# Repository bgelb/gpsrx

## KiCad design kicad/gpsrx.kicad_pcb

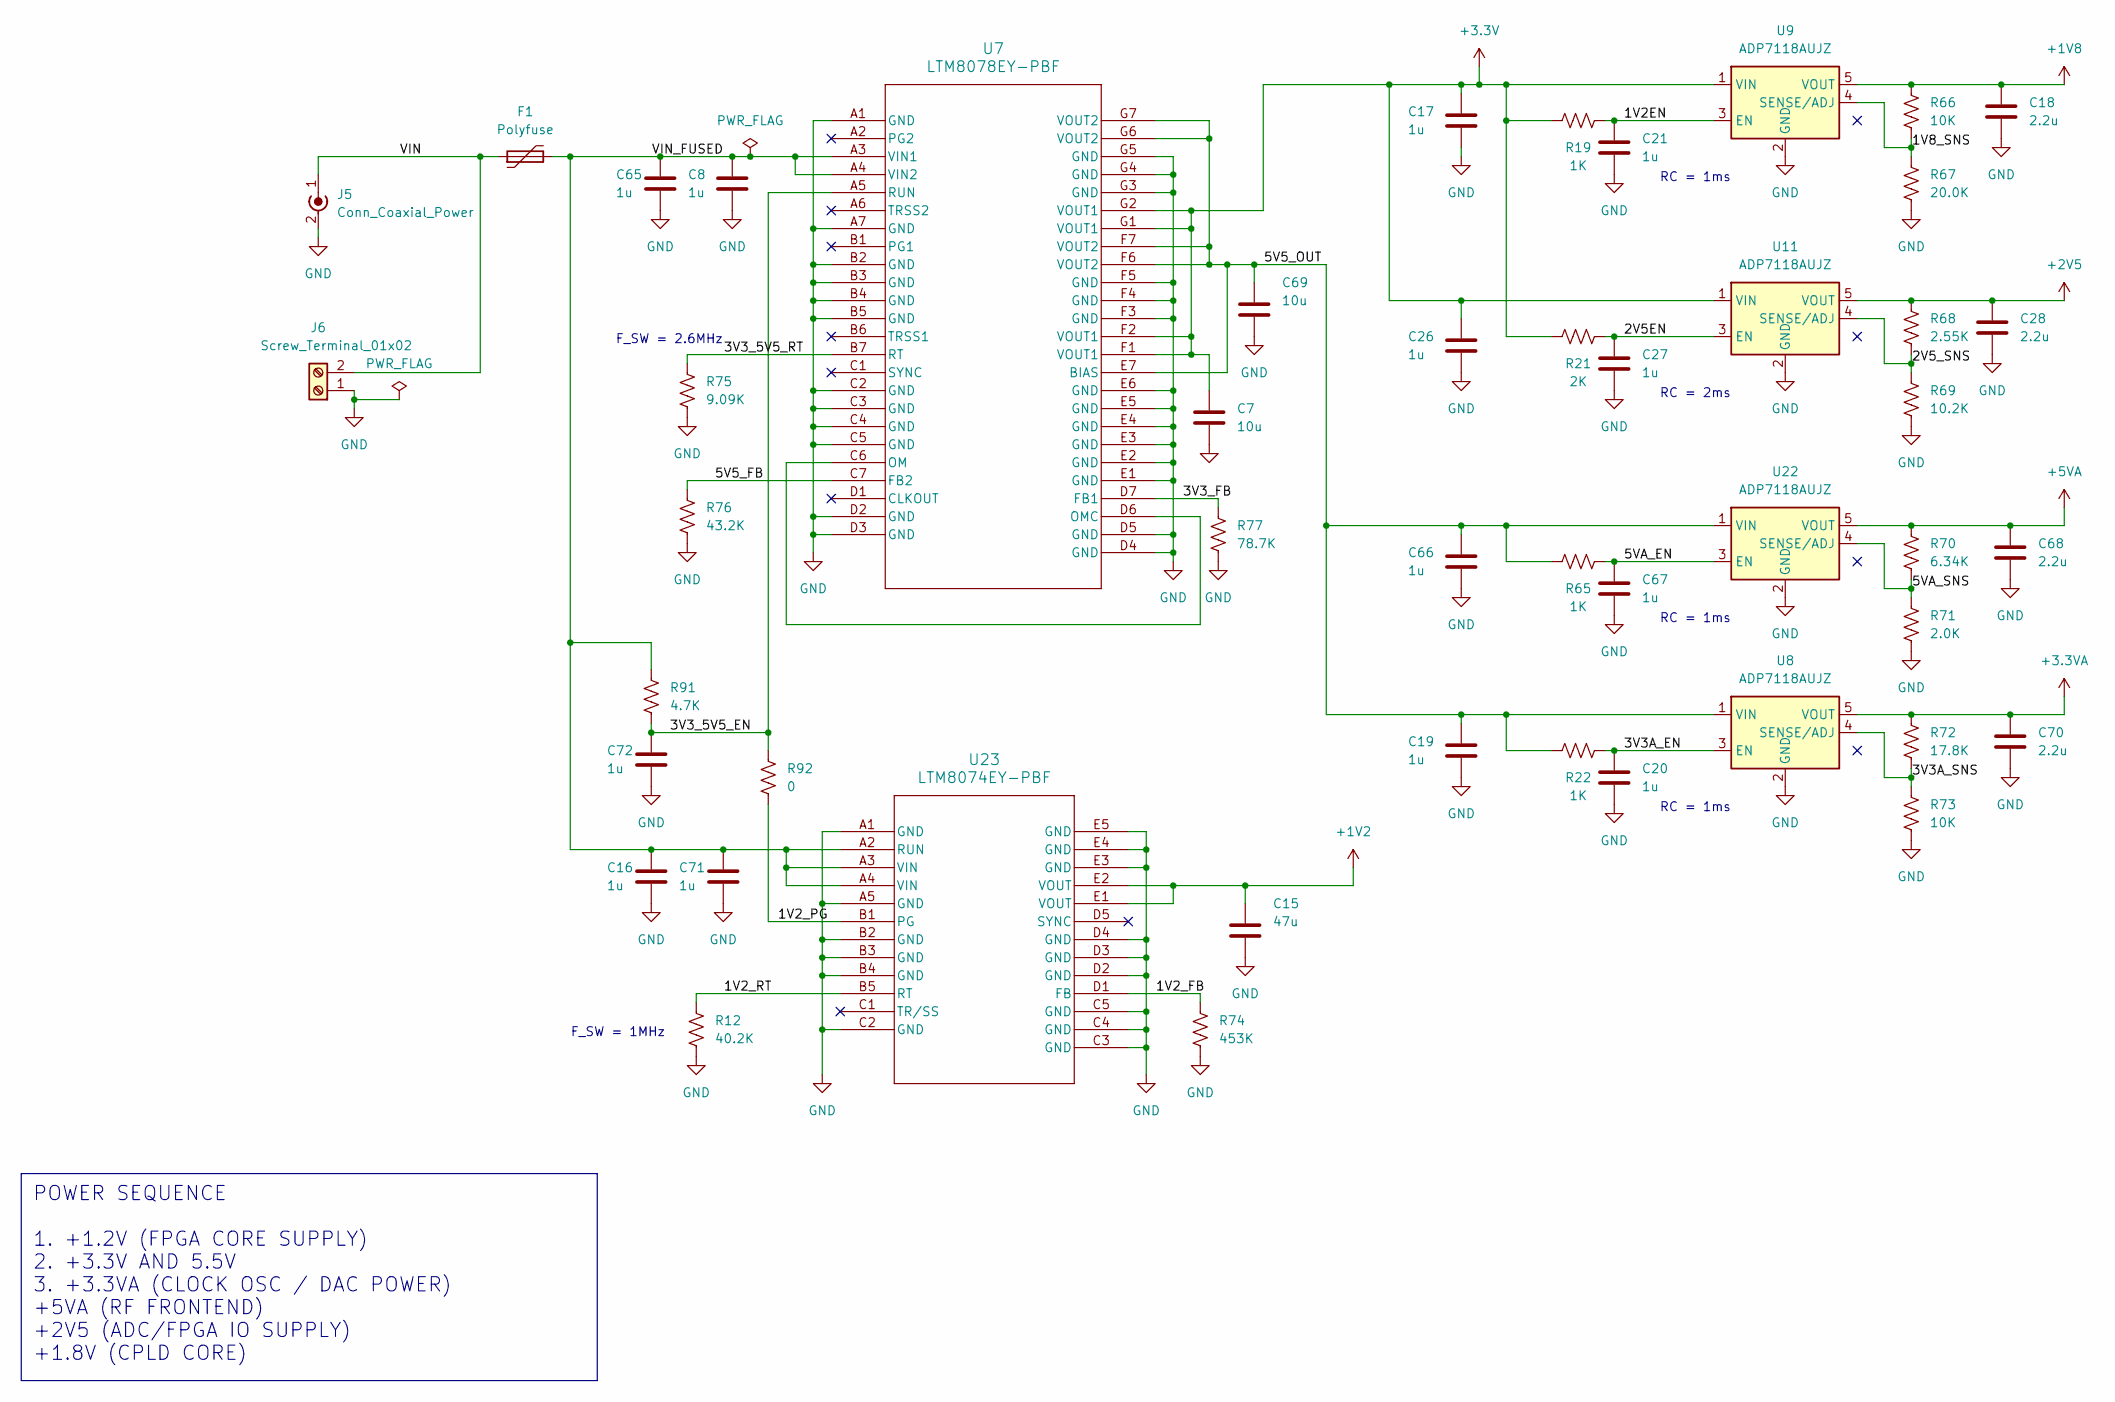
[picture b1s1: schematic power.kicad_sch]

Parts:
C7, C69: 10u; C_0805_2012Metric_Pad1.18x1.45mm_HandSolder
C8, C16, C17, C19, C20, C21, C26, C27, C65, C66, C67, C71, C72: 1u; C_0603_1608Metric_Pad1.08x0.95mm_HandSolder
C15: 47u; C_0805_2012Metric_Pad1.18x1.45mm_HandSolder
C18, C28, C68, C70: 2.2u; C_0603_1608Metric_Pad1.08x0.95mm_HandSolder
F1: Polyfuse; Fuse_2920_7451Metric_Pad2.10x5.45mm_HandSolder
J5: Conn_Coaxial_Power; BarrelJack_CUI_PJ-063AH_Horizontal
J6: Screw_Terminal_01x02; TerminalBlock_Phoenix_MKDS-1,5-2_1x02_P5.00mm_Horizontal
R12: 40.2K; R_0603_1608Metric_Pad0.98x0.95mm_HandSolder
R19, R22, R65: 1K; R_0603_1608Metric_Pad0.98x0.95mm_HandSolder
R21: 2K; R_0603_1608Metric_Pad0.98x0.95mm_HandSolder
R66, R73: 10K; R_0603_1608Metric_Pad0.98x0.95mm_HandSolder
R67: 20.0K; R_0603_1608Metric_Pad0.98x0.95mm_HandSolder
R68: 2.55K; R_0603_1608Metric_Pad0.98x0.95mm_HandSolder
R69: 10.2K; R_0603_1608Metric_Pad0.98x0.95mm_HandSolder
R70: 6.34K; R_0603_1608Metric_Pad0.98x0.95mm_HandSolder
R71: 2.0K; R_0603_1608Metric_Pad0.98x0.95mm_HandSolder
R72: 17.8K; R_0603_1608Metric_Pad0.98x0.95mm_HandSolder
R74: 453K; R_0603_1608Metric_Pad0.98x0.95mm_HandSolder
R75: 9.09K; R_0603_1608Metric_Pad0.98x0.95mm_HandSolder
R76: 43.2K; R_0603_1608Metric_Pad0.98x0.95mm_HandSolder
R77: 78.7K; R_0603_1608Metric_Pad0.98x0.95mm_HandSolder
R91: 4.7K; R_0603_1608Metric_Pad0.98x0.95mm_HandSolder
R92: 0; R_0603_1608Metric_Pad0.98x0.95mm_HandSolder
U7: LTM8078EY-PBF; LTM8078IY-PBF_ADI
U8, U9, U11, U22: ADP7118AUJZ; UJ_5_ADI
U23: LTM8074EY-PBF; 05-08-1566_ADI

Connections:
+1V2: C15.1, U23.E1 (VOUT), U23.E2 (VOUT); also elsewhere on the board
+1V8: C18.1, R66.1, U9.5 (VOUT); also elsewhere on the board
+2V5: C28.1, R68.1, U11.5 (VOUT); also elsewhere on the board
+3.3VA: C70.1, R72.1, U8.5 (VOUT); also elsewhere on the board
+5VA: C68.1, R70.1, U22.5 (VOUT); also elsewhere on the board
/Power/1V2EN: C21.1, R19.2, U9.3 (EN)
/Power/1V2_FB: R74.1, U23.D1 (FB)
/Power/1V2_PG: R92.2, U23.B1 (PG)
/Power/1V2_RT: R12.1, U23.B5 (RT)
/Power/1V8_SNS: R66.2, R67.1, U9.4 (SENSE/ADJ)
/Power/2V5EN: C27.1, R21.2, U11.3 (EN)
/Power/2V5_SNS: R68.2, R69.1, U11.4 (SENSE/ADJ)
/Power/3V3A_EN: C20.1, R22.2, U8.3 (EN)
/Power/3V3A_SNS: R72.2, R73.1, U8.4 (SENSE/ADJ)
/Power/3V3_5V5_EN: C72.1, R91.2, R92.1, U7.A5 (RUN)
/Power/3V3_5V5_RT: R75.1, U7.B7 (RT)
/Power/3V3_FB: R77.1, U7.D7 (FB1)
/Power/5V5_FB: R76.1, U7.C7 (FB2)
/Power/5V5_OUT: C19.1, C66.1, C69.1, R22.1, R65.1, U7.E7 (BIAS), U7.F6 (VOUT2), U7.F7 (VOUT2), U7.G6 (VOUT2), U7.G7 (VOUT2), U8.1 (VIN), U22.1 (VIN)
/Power/5VA_EN: C67.1, R65.2, U22.3 (EN)
/Power/5VA_SNS: R70.2, R71.1, U22.4 (SENSE/ADJ)
/Power/VIN: F1.1, J5.1 (In), J6.2
/Power/VIN_FUSED: C8.1, C16.1, C65.1, C71.1, F1.2, R91.1, U7.A3 (VIN1), U7.A4 (VIN2), U23.A2 (RUN), U23.A3 (VIN), U23.A4 (VIN)
GND: C7.2, C8.2, C15.2, C16.2, C17.2, C18.2, C19.2, C20.2, C21.2, C26.2, C27.2, C28.2, C65.2, C66.2, C67.2, C68.2, C69.2, C70.2, C71.2, C72.2, J5.2 (Ext), J6.1, R12.2, R67.2, R69.2, R71.2, R73.2, R74.2, R75.2, R76.2, R77.2, U7.A1 (GND), U7.A7 (GND), U7.B2 (GND), U7.B3 (GND), U7.B4 (GND), U7.B5 (GND), U7.C2 (GND), U7.C3 (GND), U7.C4 (GND), U7.C5 (GND), U7.D2 (GND), U7.D3 (GND), U7.D4 (GND), U7.D5 (GND), U7.E1 (GND), U7.E2 (GND), U7.E3 (GND), U7.E4 (GND), U7.E5 (GND), U7.E6 (GND), U7.F3 (GND), U7.F4 (GND), U7.F5 (GND), U7.G3 (GND), U7.G4 (GND), U7.G5 (GND), U8.2 (GND), U9.2 (GND), U11.2 (GND), U22.2 (GND), U23.A1 (GND), U23.A5 (GND), U23.B2 (GND), U23.B3 (GND), U23.B4 (GND), U23.C2 (GND), U23.C3 (GND), U23.C4 (GND), U23.C5 (GND), U23.D2 (GND), U23.D3 (GND), U23.D4 (GND), U23.E3 (GND), U23.E4 (GND), U23.E5 (GND); also elsewhere on the board
unnamed: U7.C6 (OM), U7.D6 (OMC)

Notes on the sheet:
POWER SEQUENCE 1. +1.2V (FPGA CORE SUPPLY) 2. +3.3V AND 5.5V 3. +3.3VA (CLOCK OSC / DAC POWER) +5VA (RF FRONTEND) +2V5 (ADC/FPGA IO SUPPLY) +1.8V (CPLD CORE)
F_SW = 2.6MHz
RC = 2ms
F_SW = 1MHz
RC = 1ms

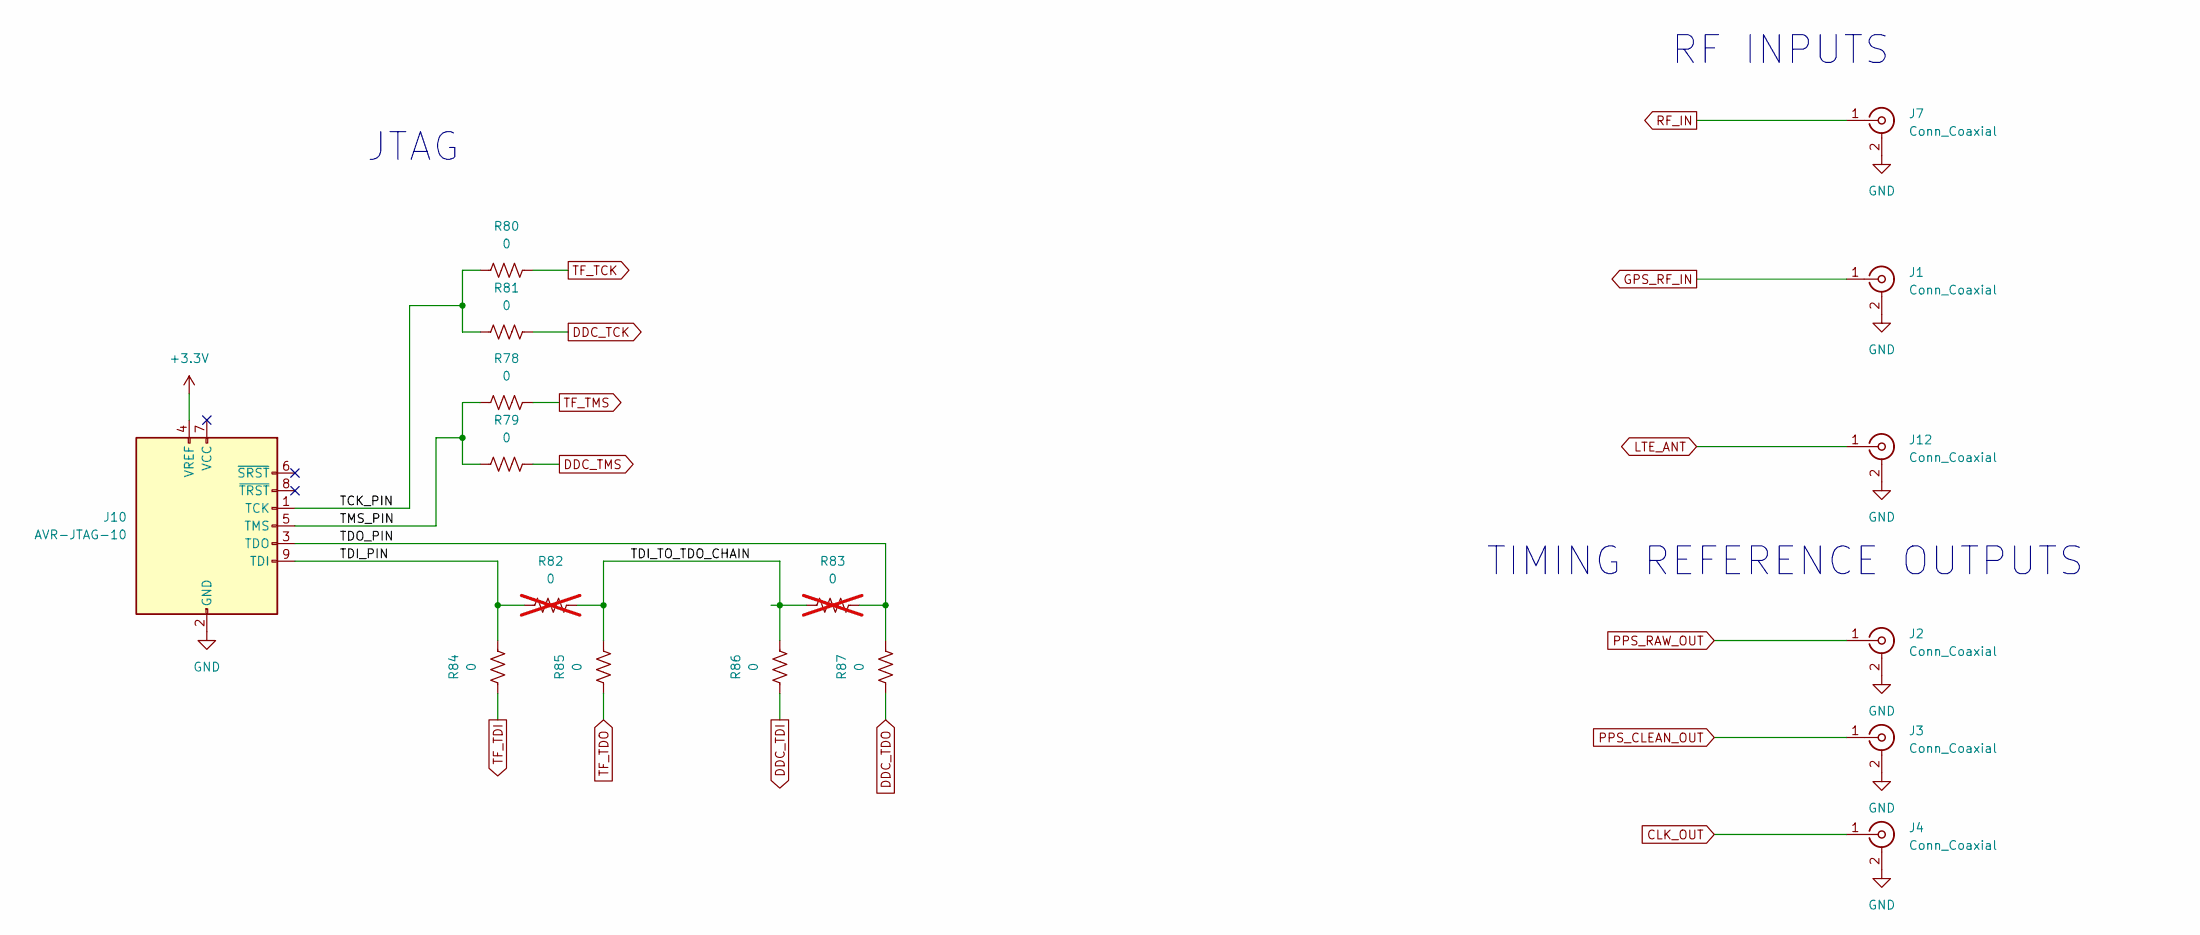
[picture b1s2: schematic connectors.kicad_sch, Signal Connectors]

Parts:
J1, J2, J3, J4, J7, J12: Conn_Coaxial; SMA_Amphenol_901-143_Horizontal
J10: AVR-JTAG-10; PinHeader_2x05_P2.54mm_Vertical
R78, R79, R80, R81, R84, R85, R86, R87: 0; R_0603_1608Metric_Pad0.98x0.95mm_HandSolder
R82, R83: 0; R_0603_1608Metric_Pad0.98x0.95mm_HandSolder; not fitted

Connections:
/Signal Connectors/TCK_PIN: J10.1 (TCK), R80.1, R81.1
/Signal Connectors/TDI_PIN: J10.9 (TDI), R82.1, R84.2
/Signal Connectors/TDI_TO_TDO_CHAIN: R82.2, R83.1, R85.2, R86.2
/Signal Connectors/TDO_PIN: J10.3 (TDO), R83.2, R87.2
/Signal Connectors/TMS_PIN: J10.5 (TMS), R78.1, R79.1
CLK_OUT: J4.1 (In); also elsewhere on the board
DDC_TCK: R81.2; also elsewhere on the board
DDC_TDI: R86.1; also elsewhere on the board
DDC_TDO: R87.1; also elsewhere on the board
DDC_TMS: R79.2; also elsewhere on the board
GND: J1.2 (Ext), J2.2 (Ext), J3.2 (Ext), J4.2 (Ext), J7.2 (Ext), J10.2 (GND), J10.10 (GND), J12.2 (Ext); also elsewhere on the board
GPS_RF_IN: J1.1 (In); also elsewhere on the board
LTE_ANT: J12.1 (In); also elsewhere on the board
PPS_CLEAN_OUT: J3.1 (In); also elsewhere on the board
PPS_RAW_OUT: J2.1 (In); also elsewhere on the board
RF_IN: J7.1 (In); also elsewhere on the board
TF_TCK: R80.2; also elsewhere on the board
TF_TDI: R84.1; also elsewhere on the board
TF_TDO: R85.1; also elsewhere on the board
TF_TMS: R78.2; also elsewhere on the board

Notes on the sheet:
JTAG
RF INPUTS
TIMING REFERENCE OUTPUTS

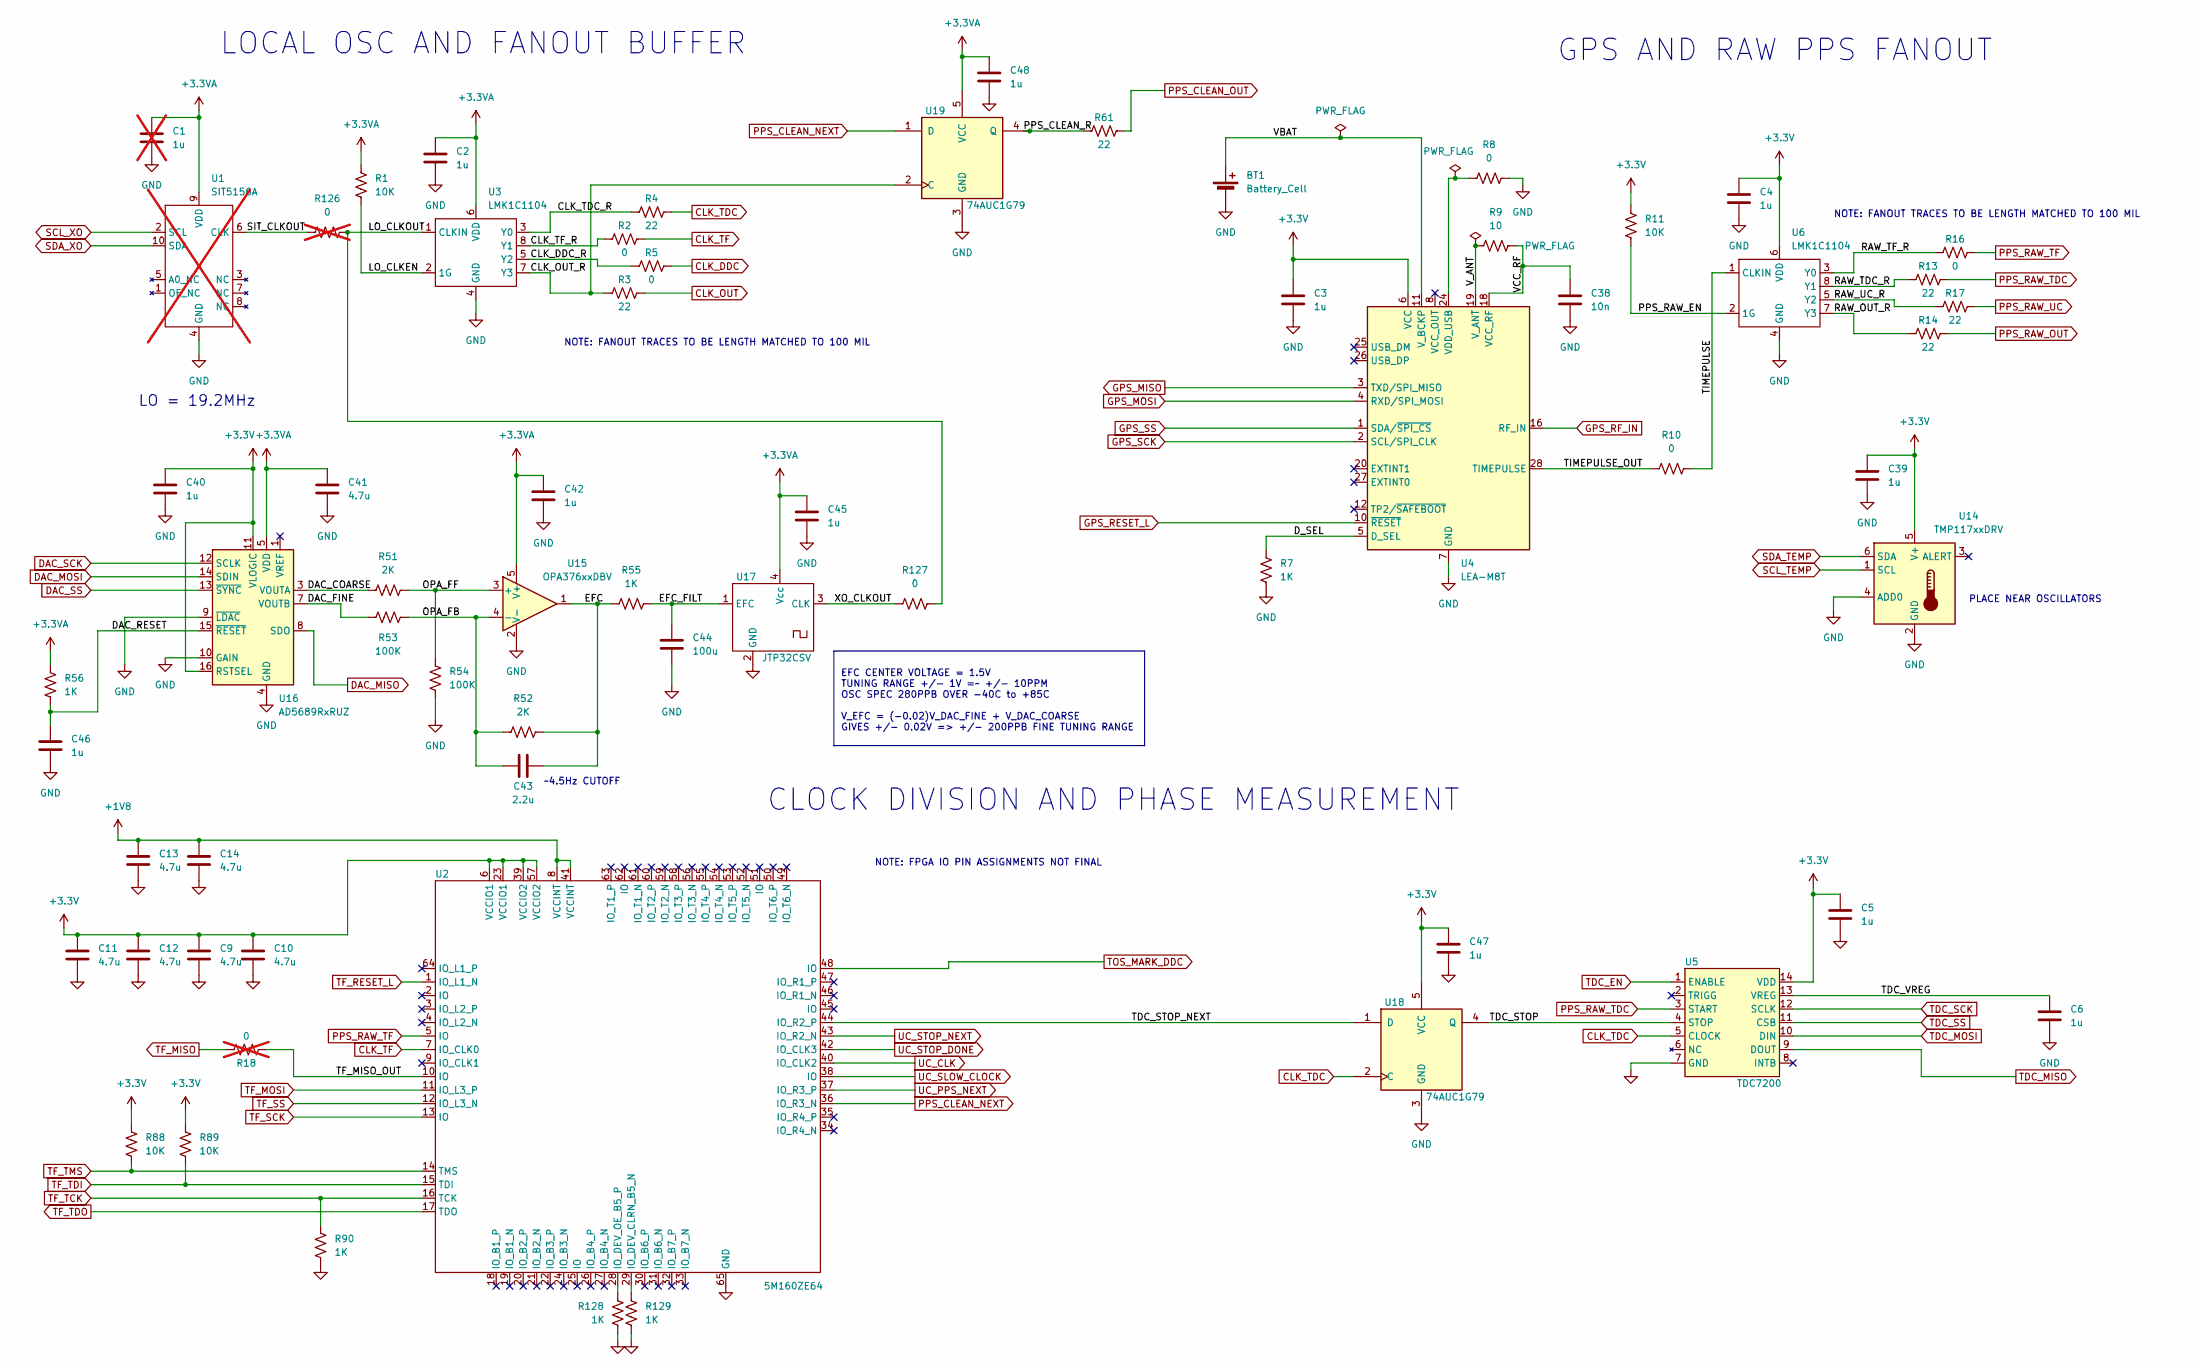
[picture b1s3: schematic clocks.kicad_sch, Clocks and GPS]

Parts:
BT1: Battery_Cell; Battery_Panasonic_CR1025-VSK_Vertical_CircularHoles
C1: 1u; C_0603_1608Metric_Pad1.08x0.95mm_HandSolder; not fitted
C2, C3, C4, C5, C6, C39, C40, C42, C45, C46, C47, C48: 1u; C_0603_1608Metric_Pad1.08x0.95mm_HandSolder
C9, C10, C11, C12, C13, C14, C41: 4.7u; C_0603_1608Metric_Pad1.08x0.95mm_HandSolder
C38: 10n; C_0603_1608Metric_Pad1.08x0.95mm_HandSolder
C43: 2.2u; C_0603_1608Metric_Pad1.08x0.95mm_HandSolder
C44: 100u; C_1206_3216Metric_Pad1.33x1.80mm_HandSolder
R1, R11, R88, R89: 10K; R_0603_1608Metric_Pad0.98x0.95mm_HandSolder
R2, R5, R8, R10, R16, R127: 0; R_0603_1608Metric_Pad0.98x0.95mm_HandSolder
R3, R4, R13, R14, R17, R61: 22; R_0603_1608Metric_Pad0.98x0.95mm_HandSolder
R7, R55, R56, R90, R128, R129: 1K; R_0603_1608Metric_Pad0.98x0.95mm_HandSolder
R9: 10; R_0603_1608Metric_Pad0.98x0.95mm_HandSolder
R18, R126: 0; R_0603_1608Metric_Pad0.98x0.95mm_HandSolder; not fitted
R51, R52: 2K; R_0603_1608Metric_Pad0.98x0.95mm_HandSolder
R53, R54: 100K; R_0603_1608Metric_Pad0.98x0.95mm_HandSolder
U1: SIT5156A; CQFN10L_5.000X3.200X0.950_SIT; not fitted
U2: 5M160ZE64; EQFP64_A-1P20_D2-4P5_INT
U3, U6: LMK1C1104; TSSOP-8_4.4x3mm_P0.65mm
U4: LEA-M8T; SMT_M8T-0_UBL
U5: TDC7200; TSSOP-14_4.4x5mm_P0.65mm
U14: TMP117xxDRV; WSON-6-1EP_2x2mm_P0.65mm_EP1x1.6mm
U15: OPA376xxDBV; SOT-23-5
U16: AD5689RxRUZ; TSSOP-16_4.4x5mm_P0.65mm
U17: JTP32CSV; Oscillator_SMD_Abracon_ASE-4Pin_3.2x2.5mm_HandSoldering
U18, U19: 74AUC1G79; SOT-23-5_HandSoldering

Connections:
+1V8: C13.1, C14.1, U2.8 (VCCINT), U2.41 (VCCINT); also elsewhere on the board
+3.3VA: C1.1, C2.1, C41.1, C42.1, C45.1, C48.1, R1.1, R56.2, U1.9 (VDD), U3.6 (VDD), U15.5 (V+), U16.5 (VDD), U17.4 (Vcc), U19.5 (VCC); also elsewhere on the board
/Clocks and GPS/CLK_DDC_R: R5.1, U3.5 (Y2)
/Clocks and GPS/CLK_OUT_R: R3.1, U3.7 (Y3), U19.2 (C)
/Clocks and GPS/CLK_TDC_R: R4.1, U3.3 (Y0)
/Clocks and GPS/CLK_TF_R: R2.1, U3.8 (Y1)
/Clocks and GPS/DAC_COARSE: R51.1, U16.3 (VOUTA)
/Clocks and GPS/DAC_FINE: R53.1, U16.7 (VOUTB)
/Clocks and GPS/DAC_RESET: C46.1, R56.1, U16.15 (~RESET)
/Clocks and GPS/D_SEL: R7.1, U4.5 (D_SEL)
/Clocks and GPS/EFC: C43.2, R52.2, R55.1, U15.1
/Clocks and GPS/EFC_FILT: C44.1, R55.2, U17.1 (EFC)
/Clocks and GPS/LO_CLKEN: R1.2, U3.2 (1G)
/Clocks and GPS/LO_CLKOUT: R126.2, R127.2, U3.1 (CLKIN)
/Clocks and GPS/OPA_FB: C43.1, R52.1, R53.2, U15.4 (-)
/Clocks and GPS/OPA_FF: R51.2, R54.2, U15.3 (+)
/Clocks and GPS/PPS_CLEAN_R: R61.1, U19.4 (Q)
/Clocks and GPS/PPS_RAW_EN: R11.2, U6.2 (1G)
/Clocks and GPS/RAW_OUT_R: R14.1, U6.7 (Y3)
/Clocks and GPS/RAW_TDC_R: R13.1, U6.8 (Y1)
/Clocks and GPS/RAW_TF_R: R16.1, U6.3 (Y0)
/Clocks and GPS/RAW_UC_R: R17.1, U6.5 (Y2)
/Clocks and GPS/SIT_CLKOUT: R126.1, U1.6 (CLK)
/Clocks and GPS/TDC_STOP: U5.4 (STOP), U18.4 (Q)
/Clocks and GPS/TDC_STOP_NEXT: U2.44 (IO_R2_P), U18.1 (D)
/Clocks and GPS/TDC_VREG: C6.1, U5.13 (VREG)
/Clocks and GPS/TF_MISO_OUT: R18.1, U2.10 (IO)
/Clocks and GPS/TIMEPULSE: R10.2, U6.1 (CLKIN)
/Clocks and GPS/TIMEPULSE_OUT: R10.1, U4.28 (TIMEPULSE)
/Clocks and GPS/VBAT: BT1.1 (+), U4.11 (V_BCKP)
/Clocks and GPS/VCC_RF: C38.1, R9.2, U4.18 (VCC_RF)
/Clocks and GPS/V_ANT: R9.1, U4.19 (V_ANT)
/Clocks and GPS/XO_CLKOUT: R127.1, U17.3 (CLK)
CLK_DDC: R5.2; also elsewhere on the board
CLK_OUT: R3.2; also elsewhere on the board
CLK_TDC: R4.2, U5.5 (CLOCK), U18.2 (C)
CLK_TF: R2.2, U2.7 (IO_CLK0)
DAC_MISO: U16.8 (SDO); also elsewhere on the board
DAC_MOSI: U16.14 (SDIN); also elsewhere on the board
DAC_SCK: U16.12 (SCLK); also elsewhere on the board
DAC_SS: U16.13 (~SYNC); also elsewhere on the board
GND: BT1.2 (-), C1.2, C2.2, C3.2, C4.2, C5.2, C6.2, C9.2, C10.2, C11.2, C12.2, C13.2, C14.2, C38.2, C39.2, C40.2, C41.2, C42.2, C44.2, C45.2, C46.2, C47.2, C48.2, R7.2, R8.2, R54.1, R90.2, R128.2, R129.2, U1.4 (GND), U2.65 (GND), U3.4 (GND), U4.7 (GND), U4.13 (GND), U4.14 (GND), U4.15 (GND), U4.17 (GND), U5.7 (GND), U6.4 (GND), U14.2 (GND), U14.4 (ADD0), U15.2 (V-), U16.4 (GND), U16.9 (~LDAC), U16.10 (GAIN), U17.2 (GND), U18.3 (GND), U19.3 (GND); also elsewhere on the board
GPS_MISO: U4.3 (TXD/SPI_MISO); also elsewhere on the board
GPS_MOSI: U4.4 (RXD/SPI_MOSI); also elsewhere on the board
GPS_RESET_L: U4.10 (~RESET); also elsewhere on the board
GPS_RF_IN: U4.16 (RF_IN); also elsewhere on the board
GPS_SCK: U4.2 (SCL/SPI_CLK); also elsewhere on the board
GPS_SS: U4.1 (SDA/~SPI_CS); also elsewhere on the board
unnamed: R129.1, U2.29 (IO_DEV_CLRN_B5_N)
unnamed: R128.1, U2.28 (IO_DEV_OE_B5_P)
unnamed: R8.1, U4.24 (VDD_USB)
PPS_CLEAN_NEXT: U2.36 (IO_R3_N), U19.1 (D)
PPS_CLEAN_OUT: R61.2; also elsewhere on the board
PPS_RAW_OUT: R14.2; also elsewhere on the board
PPS_RAW_TDC: R13.2, U5.3 (START)
PPS_RAW_TF: R16.2, U2.5 (IO)
PPS_RAW_UC: R17.2; also elsewhere on the board
SCL_TEMP: U14.1 (SCL); also elsewhere on the board
SCL_XO: U1.2 (SCL); also elsewhere on the board
SDA_TEMP: U14.6 (SDA); also elsewhere on the board
SDA_XO: U1.10 (SDA); also elsewhere on the board
TDC_EN: U5.1 (ENABLE); also elsewhere on the board
TDC_MISO: U5.9 (DOUT); also elsewhere on the board
TDC_MOSI: U5.10 (DIN); also elsewhere on the board
TDC_SCK: U5.12 (SCLK); also elsewhere on the board
TDC_SS: U5.11 (CSB); also elsewhere on the board
TF_MISO: R18.2; also elsewhere on the board
TF_MOSI: U2.11 (IO_L3_P); also elsewhere on the board
TF_RESET_L: U2.1 (IO_L1_N); also elsewhere on the board
TF_SCK: U2.13 (IO); also elsewhere on the board
TF_SS: U2.12 (IO_L3_N); also elsewhere on the board
TF_TCK: R90.1, U2.16 (TCK); also elsewhere on the board
TF_TDI: R89.2, U2.15 (TDI); also elsewhere on the board
TF_TDO: U2.17 (TDO); also elsewhere on the board
TF_TMS: R88.2, U2.14 (TMS); also elsewhere on the board
TOS_MARK_DDC: U2.48 (IO); also elsewhere on the board
UC_CLK: U2.40 (IO_CLK2); also elsewhere on the board
UC_PPS_NEXT: U2.37 (IO_R3_P); also elsewhere on the board
UC_SLOW_CLOCK: U2.38 (IO); also elsewhere on the board
UC_STOP_DONE: U2.42 (IO_CLK3); also elsewhere on the board
UC_STOP_NEXT: U2.43 (IO_R2_N); also elsewhere on the board

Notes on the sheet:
LO = 19.2MHz
NOTE: FANOUT TRACES TO BE LENGTH MATCHED TO 100 MIL
GPS AND RAW PPS FANOUT
NOTE: FPGA IO PIN ASSIGNMENTS NOT FINAL
CLOCK DIVISION AND PHASE MEASUREMENT
LOCAL OSC AND FANOUT BUFFER
PLACE NEAR OSCILLATORS
~4.5Hz CUTOFF
EFC CENTER VOLTAGE = 1.5V TUNING RANGE +/- 1V =~ +/- 10PPM OSC SPEC 280PPB OVER -40C to +85C V_EFC = (-0.02)V_DAC_FINE + V_DAC_COARSE GIVES +/- 0.02V => +/- 200PPB FINE TUNING RANGE

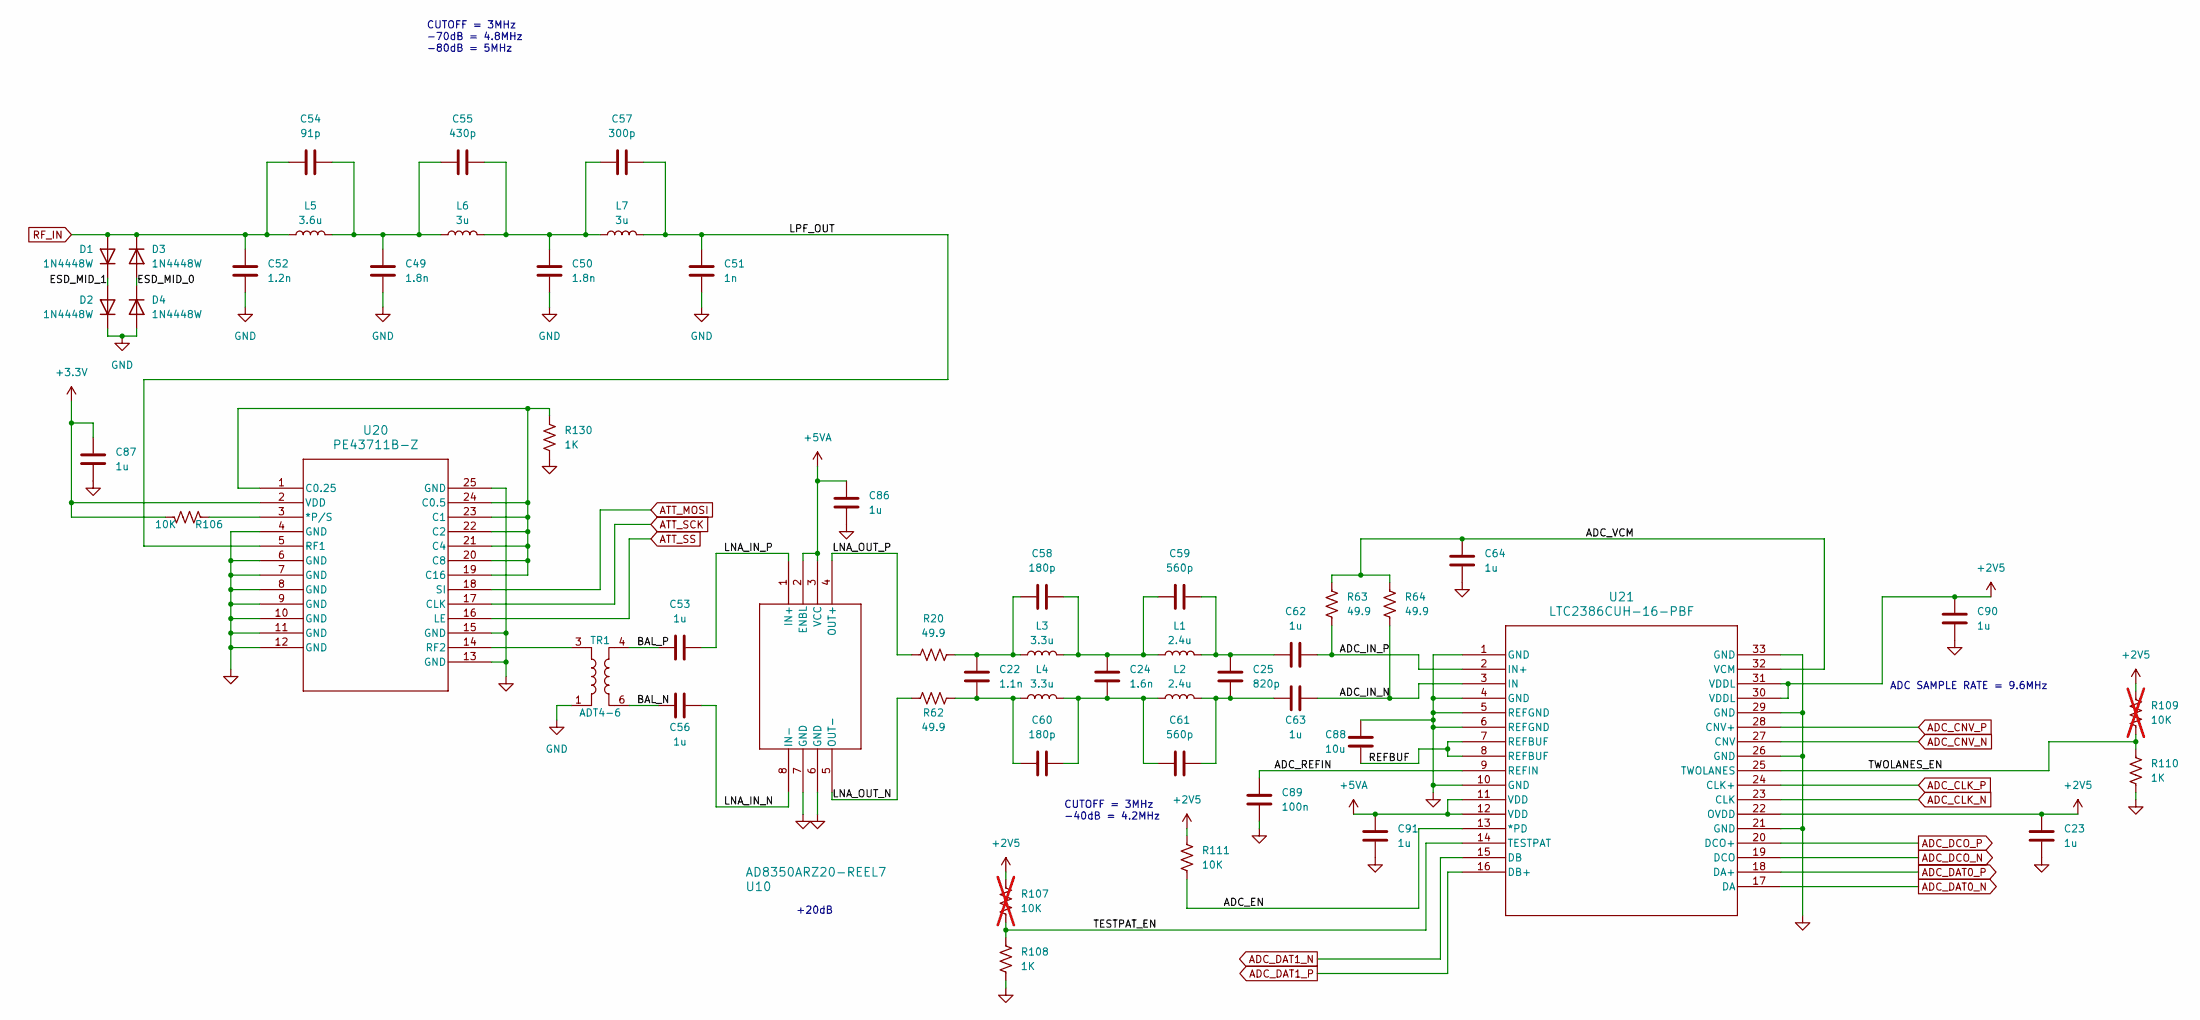
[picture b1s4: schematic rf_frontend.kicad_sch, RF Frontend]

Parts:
C22: 1.1n; C_0805_2012Metric_Pad1.18x1.45mm_HandSolder
C23, C53, C56, C62, C63, C64, C86, C87, C90, C91: 1u; C_0603_1608Metric_Pad1.08x0.95mm_HandSolder
C24: 1.6n; C_0805_2012Metric_Pad1.18x1.45mm_HandSolder
C25: 820p; C_0805_2012Metric_Pad1.18x1.45mm_HandSolder
C49, C50: 1.8n; C_0805_2012Metric_Pad1.18x1.45mm_HandSolder
C51: 1n; C_0805_2012Metric_Pad1.18x1.45mm_HandSolder
C52: 1.2n; C_0805_2012Metric_Pad1.18x1.45mm_HandSolder
C54: 91p; C_0805_2012Metric_Pad1.18x1.45mm_HandSolder
C55: 430p; C_0805_2012Metric_Pad1.18x1.45mm_HandSolder
C57: 300p; C_0805_2012Metric_Pad1.18x1.45mm_HandSolder
C58, C60: 180p; C_0805_2012Metric_Pad1.18x1.45mm_HandSolder
C59, C61: 560p; C_0805_2012Metric_Pad1.18x1.45mm_HandSolder
C88: 10u; C_0805_2012Metric_Pad1.18x1.45mm_HandSolder
C89: 100n; C_0603_1608Metric_Pad1.08x0.95mm_HandSolder
D1, D2, D3, D4: 1N4448W; D_SOD-123
L1, L2: 2.4u; L_1812_4532Metric_Pad1.30x3.40mm_HandSolder
L3, L4: 3.3u; L_1812_4532Metric_Pad1.30x3.40mm_HandSolder
L5: 3.6u; L_1812_4532Metric_Pad1.30x3.40mm_HandSolder
L6, L7: 3u; L_1812_4532Metric_Pad1.30x3.40mm_HandSolder
R20, R62, R63, R64: 49.9; R_0603_1608Metric_Pad0.98x0.95mm_HandSolder
R106, R111: 10K; R_0603_1608Metric_Pad0.98x0.95mm_HandSolder
R107, R109: 10K; R_0603_1608Metric_Pad0.98x0.95mm_HandSolder; not fitted
R108, R110, R130: 1K; R_0603_1608Metric_Pad0.98x0.95mm_HandSolder
TR1: ADT4-6; Mini-Circuits_CD637_H5.23mm
U10: AD8350ARZ20-REEL7; SOIC127P600X175-8N
U20: PE43711B-Z; QFN24_4X4_PSM
U21: LTC2386CUH-16-PBF; UH_32_ADI

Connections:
+2V5: C23.1, C90.1, R107.1, R109.1, R111.1, U21.22 (OVDD), U21.30 (VDDL), U21.31 (VDDL); also elsewhere on the board
+5VA: C86.1, C91.1, U10.2 (ENBL), U10.3 (VCC), U21.11 (VDD), U21.12 (VDD); also elsewhere on the board
/RF Frontend/ADC_EN: R111.2, U21.13 (*PD)
/RF Frontend/ADC_IN_N: C63.2, R64.2, U21.3 (IN)
/RF Frontend/ADC_IN_P: C62.2, R63.2, U21.2 (IN+)
/RF Frontend/ADC_REFIN: C89.1, U21.9 (REFIN)
/RF Frontend/ADC_VCM: C64.1, R63.1, R64.1, U21.32 (VCM)
/RF Frontend/BAL_N: C56.1, TR1.6
/RF Frontend/BAL_P: C53.1, TR1.4
/RF Frontend/ESD_MID_0: D3.2 (A), D4.1 (K)
/RF Frontend/ESD_MID_1: D1.1 (K), D2.2 (A)
/RF Frontend/LNA_IN_N: C56.2, U10.8 (IN-)
/RF Frontend/LNA_IN_P: C53.2, U10.1 (IN+)
/RF Frontend/LNA_OUT_N: R62.1, U10.5 (OUT-)
/RF Frontend/LNA_OUT_P: R20.1, U10.4 (OUT+)
/RF Frontend/LPF_OUT: C51.1, C57.2, L7.2, U20.5 (RF1)
/RF Frontend/REFBUF: C88.2, U21.7 (REFBUF), U21.8 (REFBUF)
/RF Frontend/TESTPAT_EN: R107.2, R108.1, U21.14 (TESTPAT)
/RF Frontend/TWOLANES_EN: R109.2, R110.1, U21.25 (TWOLANES)
ADC_CLK_N: U21.23 (CLK); also elsewhere on the board
ADC_CLK_P: U21.24 (CLK+); also elsewhere on the board
ADC_CNV_N: U21.27 (CNV); also elsewhere on the board
ADC_CNV_P: U21.28 (CNV+); also elsewhere on the board
ADC_DAT0_N: U21.17 (DA); also elsewhere on the board
ADC_DAT0_P: U21.18 (DA+); also elsewhere on the board
ADC_DAT1_N: U21.15 (DB); also elsewhere on the board
ADC_DAT1_P: U21.16 (DB+); also elsewhere on the board
ADC_DCO_N: U21.19 (DCO); also elsewhere on the board
ADC_DCO_P: U21.20 (DCO+); also elsewhere on the board
ATT_MOSI: U20.18 (SI); also elsewhere on the board
ATT_SCK: U20.17 (CLK); also elsewhere on the board
ATT_SS: U20.16 (LE); also elsewhere on the board
GND: C23.2, C49.2, C50.2, C51.2, C52.2, C64.2, C86.2, C87.2, C88.1, C89.2, C90.2, C91.2, D2.1 (K), D4.2 (A), R108.2, R110.2, R130.2, TR1.1, U10.6 (GND), U10.7 (GND), U20.4 (GND), U20.6 (GND), U20.7 (GND), U20.8 (GND), U20.9 (GND), U20.10 (GND), U20.11 (GND), U20.12 (GND), U20.13 (GND), U20.15 (GND), U20.25 (GND), U21.1 (GND), U21.4 (GND), U21.5 (REFGND), U21.6 (REFGND), U21.10 (GND), U21.21 (GND), U21.26 (GND), U21.29 (GND), U21.33 (GND); also elsewhere on the board
unnamed: C22.1, C58.1, L3.1, R20.2
unnamed: C22.2, C60.1, L4.1, R62.2
unnamed: C24.1, C58.2, C59.1, L1.1, L3.2
unnamed: C24.2, C60.2, C61.1, L2.1, L4.2
unnamed: C25.1, C59.2, C62.1, L1.2
unnamed: C25.2, C61.2, C63.1, L2.2
unnamed: C49.1, C54.2, C55.1, L5.2, L6.1
unnamed: C50.1, C55.2, C57.1, L6.2, L7.1
unnamed: R106.1, U20.3 (*P/S)
unnamed: R130.1, U20.1 (C0.25), U20.19 (C16), U20.20 (C8), U20.21 (C4), U20.22 (C2), U20.23 (C1), U20.24 (C0.5)
unnamed: TR1.3, U20.14 (RF2)
RF_IN: C52.1, C54.1, D1.2 (A), D3.1 (K), L5.1; also elsewhere on the board

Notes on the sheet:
CUTOFF = 3MHz -70dB = 4.8MHz -80dB = 5MHz
CUTOFF = 3MHz -40dB = 4.2MHz
+20dB
ADC SAMPLE RATE = 9.6MHz
